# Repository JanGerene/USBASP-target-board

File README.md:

# USBASP-target-board
USBASP programming boards for use with USBASP-H6 module

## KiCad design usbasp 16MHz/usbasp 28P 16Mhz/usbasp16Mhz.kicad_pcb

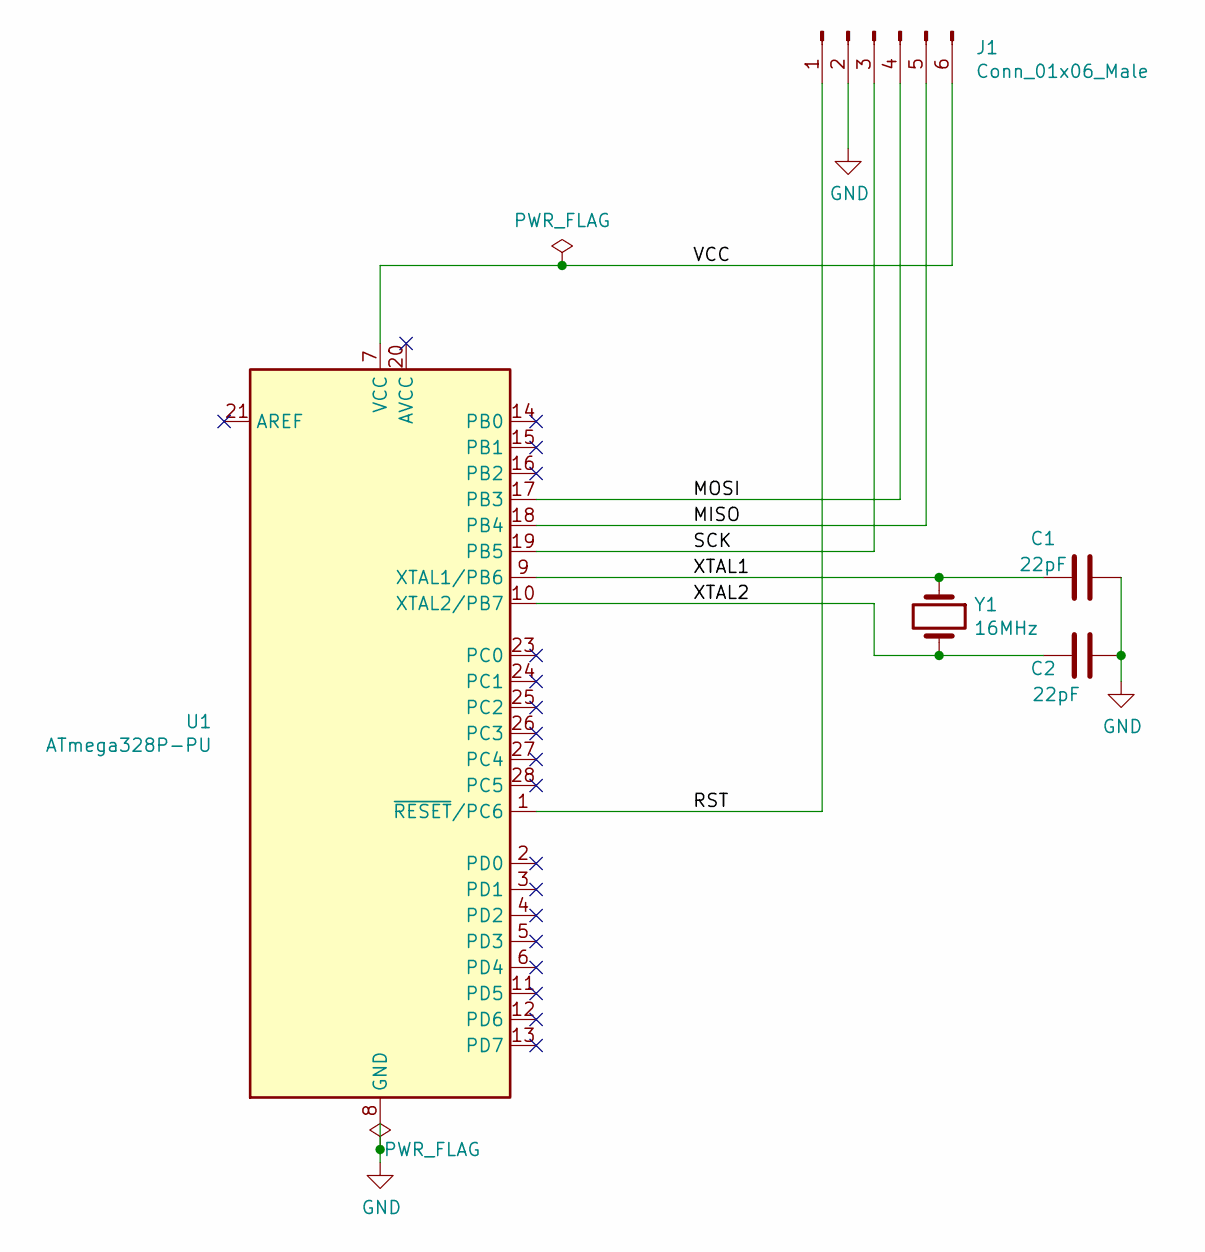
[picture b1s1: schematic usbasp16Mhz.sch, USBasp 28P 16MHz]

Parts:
C1, C2: 22pF; C_Disc_D5.0mm_W2.5mm_P2.50mm
J1: Conn_01x06_Male; PinHeader_2x03_P2.54mm_Vertical
U1: ATmega328P-PU; DIP-28_W7.62mm
Y1: 16MHz; Crystal_HC49-U_Vertical

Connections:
/MISO: J1.5, U1.18 (PB4)
/MOSI: J1.4, U1.17 (PB3)
/RST: J1.1, U1.1 (~RESET~/PC6)
/SCK: J1.3, U1.19 (PB5)
/VCC: J1.6, U1.7 (VCC)
/XTAL1: C1.2, U1.9 (XTAL1/PB6), Y1.1
GND: C1.1, C2.1, J1.2, U1.8 (GND), U1.22 (GND)
unnamed: C2.2, U1.10 (XTAL2/PB7), Y1.2

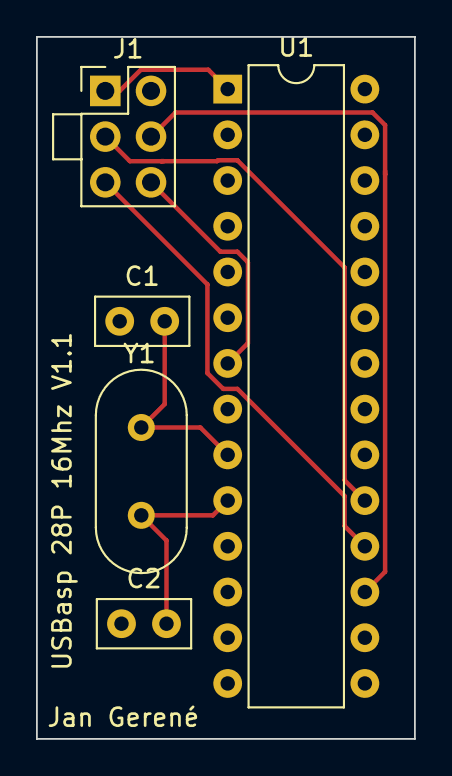
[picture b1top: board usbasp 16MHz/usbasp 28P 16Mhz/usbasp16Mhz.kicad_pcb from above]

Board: 2 copper layers, 21.0 x 39.0 mm, 5 parts (0 on the bottom side), 8 nets.

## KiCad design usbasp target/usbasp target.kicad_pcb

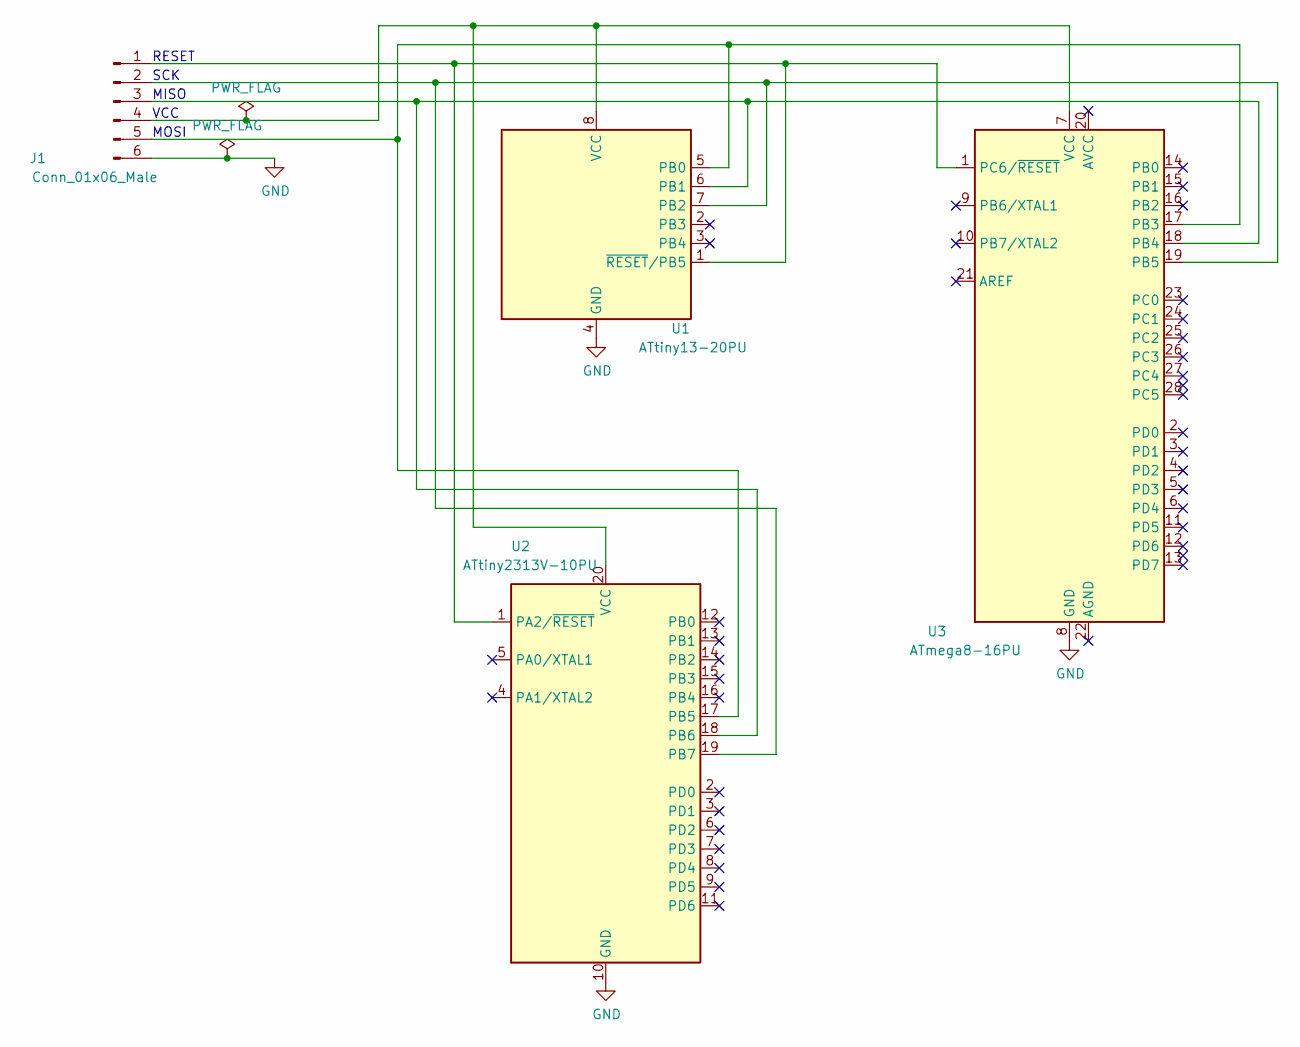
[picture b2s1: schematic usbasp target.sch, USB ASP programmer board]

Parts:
J1: Conn_01x06_Male; PinHeader_2x03_P2.54mm_Vertical
U1: ATtiny13-20PU; DIP-8_W7.62mm
U2: ATtiny2313V-10PU; DIP-20_W7.62mm
U3: ATmega8-16PU; DIP-28_W7.62mm

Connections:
GND: J1.6, U1.4 (GND), U2.10 (GND), U3.8 (GND)
unnamed: J1.1, U1.1 (~RESET~/PB5), U2.1 (PA2/~RESET), U3.1 (PC6/~RESET)
unnamed: J1.2, U1.7 (PB2), U2.19 (PB7), U3.19 (PB5)
unnamed: J1.3, U1.6 (PB1), U2.18 (PB6), U3.18 (PB4)
unnamed: J1.4, U1.8 (VCC), U2.20 (VCC), U3.7 (VCC)
unnamed: J1.5, U1.5 (PB0), U2.17 (PB5), U3.17 (PB3)

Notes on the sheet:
SCK
RESET
MISO
VCC
MOSI

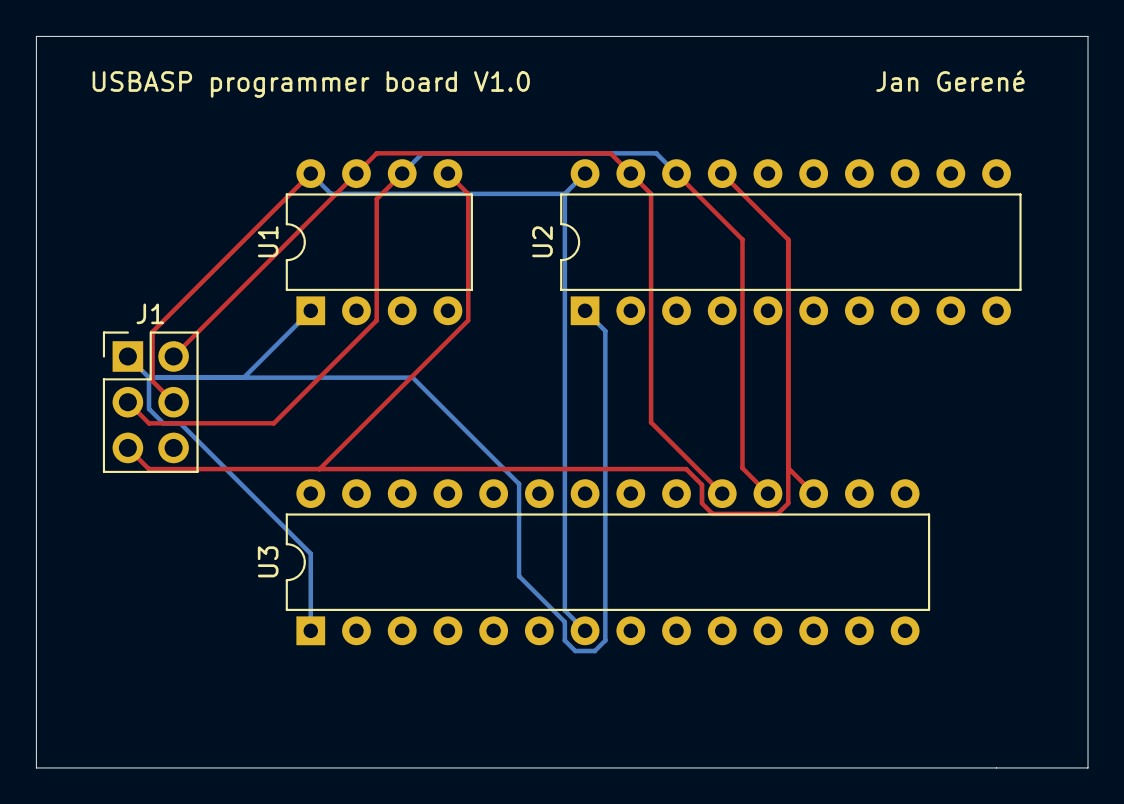
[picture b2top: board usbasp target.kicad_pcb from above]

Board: 2 copper layers, 58.4 x 40.6 mm, 4 parts (0 on the bottom side), 6 nets.

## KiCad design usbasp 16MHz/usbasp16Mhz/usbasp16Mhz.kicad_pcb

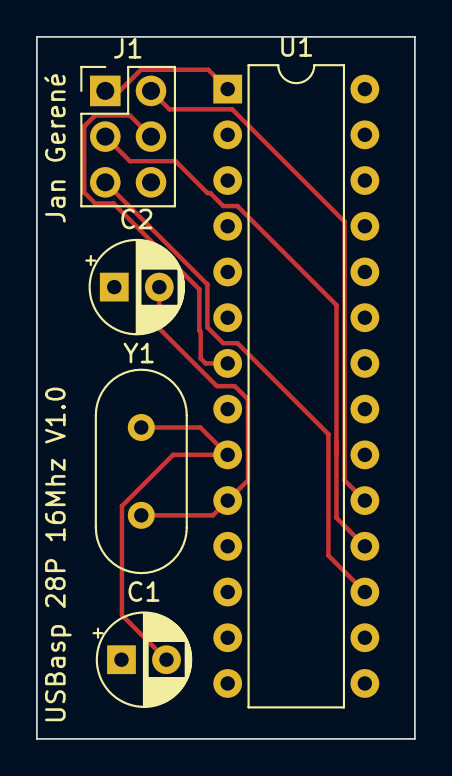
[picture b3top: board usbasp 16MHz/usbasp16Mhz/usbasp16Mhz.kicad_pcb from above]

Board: 2 copper layers, 21.0 x 39.0 mm, 5 parts (0 on the bottom side), 8 nets.

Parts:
C1, C2: 22pF; CP_Radial_D5.0mm_P2.50mm
J1: Conn_01x06_Male; PinHeader_2x03_P2.54mm_Vertical
U1: ATmega328P-PU; DIP-28_W7.62mm
Y1: 16MHz; Crystal_HC49-U_Vertical

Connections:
GND: C1.1, C2.1, J1.6, U1.8, U1.22
unnamed: C1.2, U1.9, Y1.1
unnamed: C2.2, U1.10, Y1.2
unnamed: J1.1, U1.1
unnamed: J1.2, U1.19
unnamed: J1.3, U1.18
unnamed: J1.4, U1.7
unnamed: J1.5, U1.17

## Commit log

2020-12-03 renamed gerbers.zip
2021-02-08 new version 16MHz
2022-11-20 new symbols
